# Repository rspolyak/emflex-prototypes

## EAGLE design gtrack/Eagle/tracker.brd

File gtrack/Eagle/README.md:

This folder contains schematic, PCB and gerber files for GSM security board.
Created using Eagle CAD version 7.7

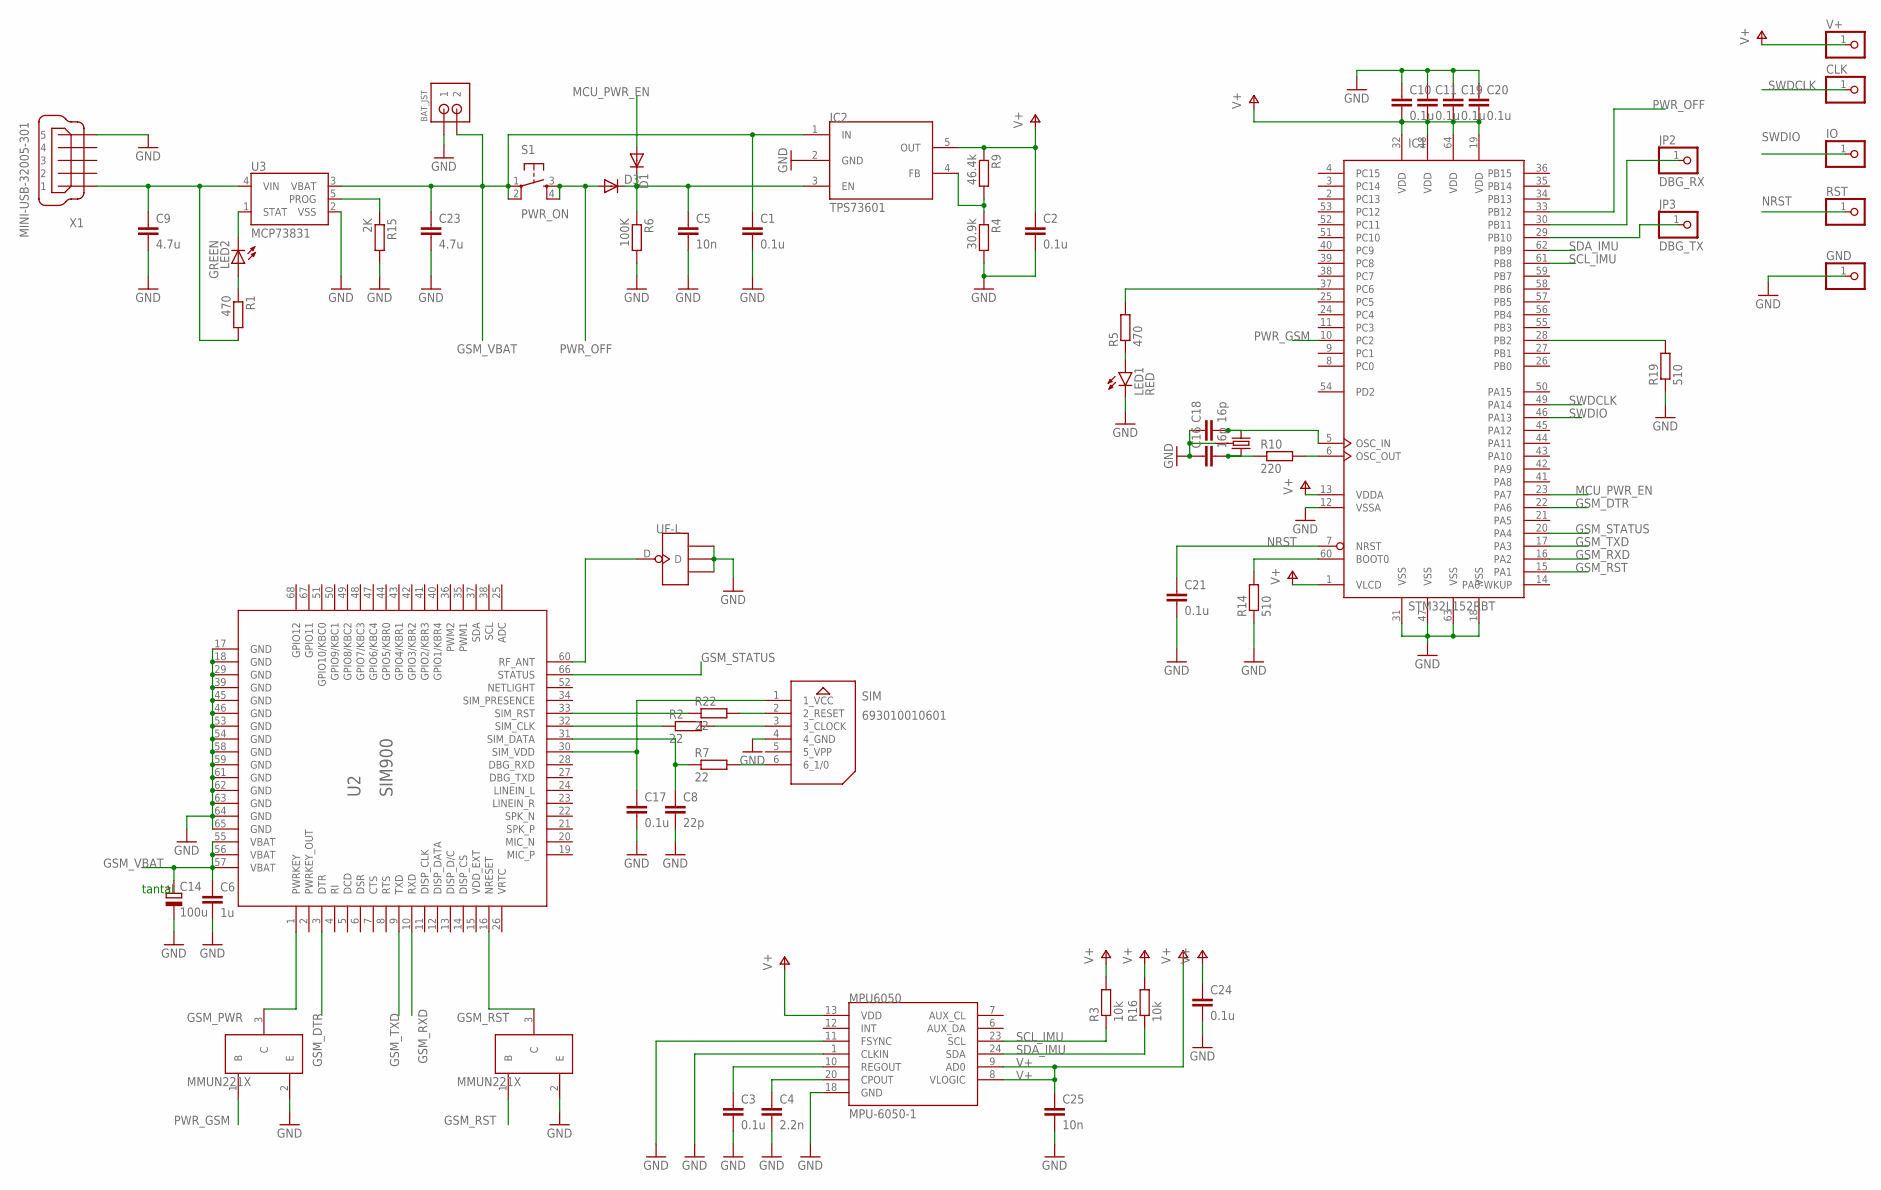
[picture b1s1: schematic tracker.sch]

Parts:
BAT_JST: JST-PH_2-PIN_HEADER; JST_B2B-PH_HEADER
C1, C2, C3, C10, C11, C17, C19, C20, C21, C24: 0.1u; C0805
C4: 2.2n; C0805
C5, C25: 10n; C0805
C6: 1u; C0805
C8: 22p; C0805
C9, C23: 4.7u; C0805
C14: 100u; C/6032-28R
C16, C18: 16p; C0603
CLK: PINHD-1X1; 1X01
CRTL: CRYSTAL-GROUNDED; CRYSTAL-SMD-5X3
D1, D3: MBR0520LT; SOD123
GND: PINHD-1X1; 1X01
GSM_PWR: MMUN221X
GSM_RST: MMUN221X
IC1: STM32L152RBT; LQFP64
IC2: TPS73601; SOT23
IO: PINHD-1X1; 1X01
JP2: DBG_RX; 1X01
JP3: DBG_TX; 1X01
LED1: RED; LED-0603
LED2: GREEN; LED-0603
MPU6050: MPU-6050-1; QFN-24-4MM2
R1, R5: 470; R0805
R2, R7, R22: 22; R0805
R3, R16: 10k; R0805
R4: 30.9k; R0805
R6: 100K; R0805
R9: 46.4k; R0805
R10: 220; R0805
R14, R19: 510; R0805
R15: 2K; R0805
RST: PINHD-1X1; 1X01
S1: PWR_ON; TACTILE-PTH
SIM: 693010010601
U2: SIM900
U3: MCP73831; SOT23-5
UF-L: ANTENNA-U-FL; 4P-U-FL
V+: PINHD-1X1; 1X01
X1: MINI-USB-32005-301; 32005-301

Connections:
BOOT1: IC1.28 (PB2), R19.2
DBG_RX: IC1.30 (PB11), JP2.1
DBG_TX: IC1.29 (PB10), JP3.1
GND: BAT_JST.P1 (1), C1.2, C2.2, C3.2, C4.2, C5.2, C6.2, C8.2, C9.2, C10.1, C11.1, C14.-, C16.1, C17.2, C18.1, C19.1, C20.1, C21.2, C23.2, C24.2, C25.2, CRTL.2 (3), CRTL.4 (3), GND.1, GSM_PWR.2 (E), GSM_RST.2 (E), IC1.12 (VSSA), IC1.18 (VSS), IC1.31 (VSS), IC1.47 (VSS), IC1.63 (VSS), IC2.2 (GND), LED1.C, MPU6050.1 (CLKIN), MPU6050.11 (FSYNC), MPU6050.18 (GND), R4.2, R6.2, R14.1, R15.2, R19.1, SIM.4 (4_GND), U2.17 (GND), U2.18 (GND), U2.29 (GND), U2.39 (GND), U2.45 (GND), U2.46 (GND), U2.53 (GND), U2.54 (GND), U2.58 (GND), U2.59 (GND), U2.61 (GND), U2.62 (GND), U2.63 (GND), U2.64 (GND), U2.65 (GND), U3.2 (VSS), UF-L.GND1, UF-L.GND2, UF-L.GND3, X1.5
GSM_DTR: IC1.22 (PA6), U2.3 (DTR)
GSM_RST: GSM_RST.1 (B), IC1.15 (PA1)
GSM_RXD: IC1.16 (PA2), U2.10 (RXD)
GSM_STATUS: IC1.20 (PA4), U2.66 (STATUS)
GSM_TXD: IC1.17 (PA3), U2.9 (TXD)
GSM_VBAT: BAT_JST.P2 (2), C1.1, C6.1, C14.+, C23.1, IC2.1 (IN), S1.1, S1.2, U2.55 (VBAT), U2.56 (VBAT), U2.57 (VBAT), U3.3 (VBAT)
MCU_PWR_EN: D1.A, IC1.23 (PA7)
unnamed: U2.60 (RF_ANT), UF-L.D
unnamed: R7.2, SIM.6 (6_1/0)
unnamed: GSM_RST.3 (C), U2.16 (NRESET)
unnamed: R2.2, SIM.3 (3_CLOCK)
unnamed: R22.2, SIM.2 (2_RESET)
unnamed: IC1.37 (PC6), R5.2
unnamed: C18.2, CRTL.3 (1), IC1.5 (OSC_IN)
unnamed: C16.2, CRTL.1 (2), R10.1
unnamed: LED2.A, R1.1
unnamed: IC2.4 (FB), R4.1, R9.2
unnamed: IC1.6 (OSC_OUT), R10.2
unnamed: IC1.60 (BOOT0), R14.2
unnamed: GSM_PWR.3 (C), U2.1 (PWRKEY)
unnamed: LED1.A, R5.1
unnamed: C4.1, MPU6050.20 (CPOUT)
unnamed: C3.1, MPU6050.10 (REGOUT)
NRST: C21.1, IC1.7 (NRST), RST.1
PROG: R15.1, U3.5 (PROG)
PWR_GSM: GSM_PWR.1 (B), IC1.10 (PC2)
PWR_OFF: D3.A, IC1.33 (PB12), S1.3, S1.4
SCL_IMU: IC1.61 (PB8), MPU6050.23 (SCL), R3.1
SDA_IMU: IC1.62 (PB9), MPU6050.24 (SDA), R16.1
SIM_CLK: R2.1, U2.32 (SIM_CLK)
SIM_DATA: C8.1, R7.1, U2.31 (SIM_DATA)
SIM_RST: R22.1, U2.33 (SIM_RST)
SIM_VDD: C17.1, SIM.1 (1_VCC), U2.30 (SIM_VDD)
STAT: LED2.C, U3.1 (STAT)
SWDCLK: CLK.1, IC1.49 (PA14)
SWDIO: IC1.46 (PA13), IO.1
V+: C2.1, C10.2, C11.2, C19.2, C20.2, C24.1, C25.1, IC1.1 (VLCD), IC1.13 (VDDA), IC1.19 (VDD), IC1.32 (VDD), IC1.48 (VDD), IC1.64 (VDD), IC2.5 (OUT), MPU6050.8 (VLOGIC), MPU6050.9 (AD0), MPU6050.13 (VDD), R3.2, R9.1, R16.2, V+.1
VCC_GSM: C5.1, D1.C, D3.C, IC2.3 (EN), R6.1
VIN1: C9.1, R1.2, U3.4 (VIN), X1.1

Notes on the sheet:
tantal

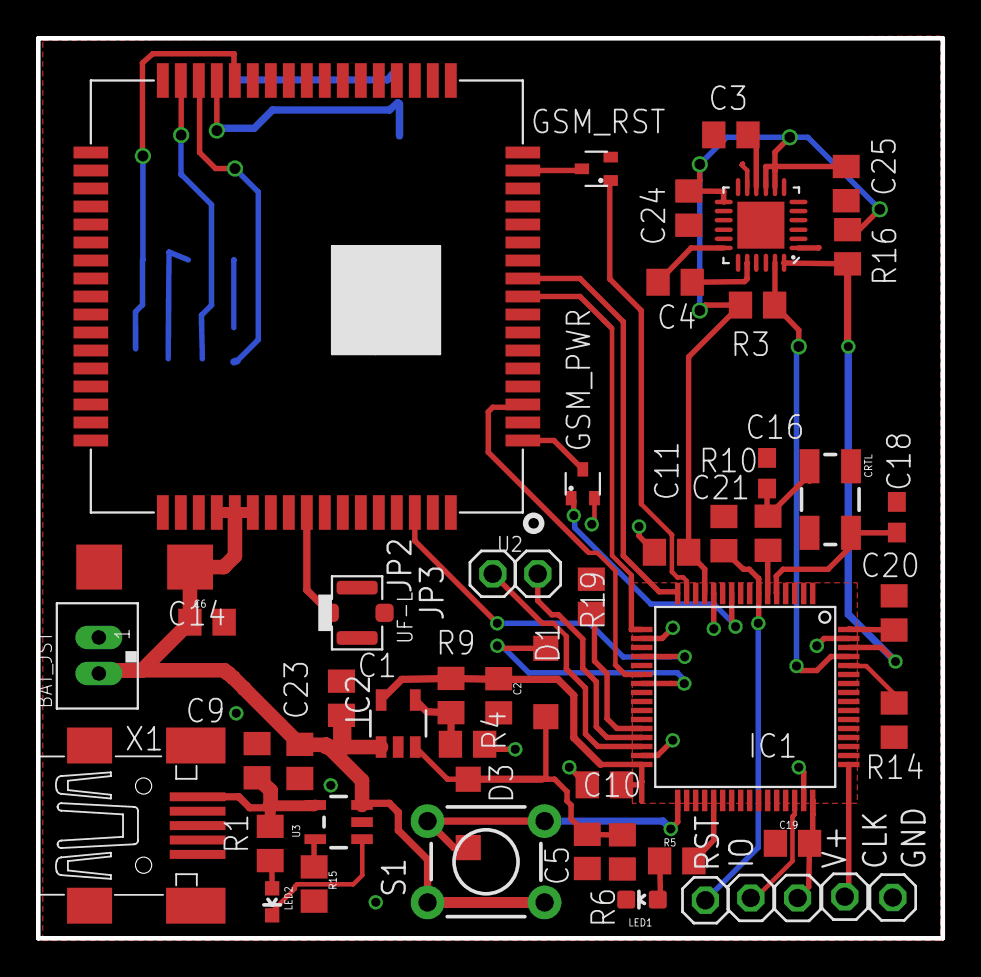
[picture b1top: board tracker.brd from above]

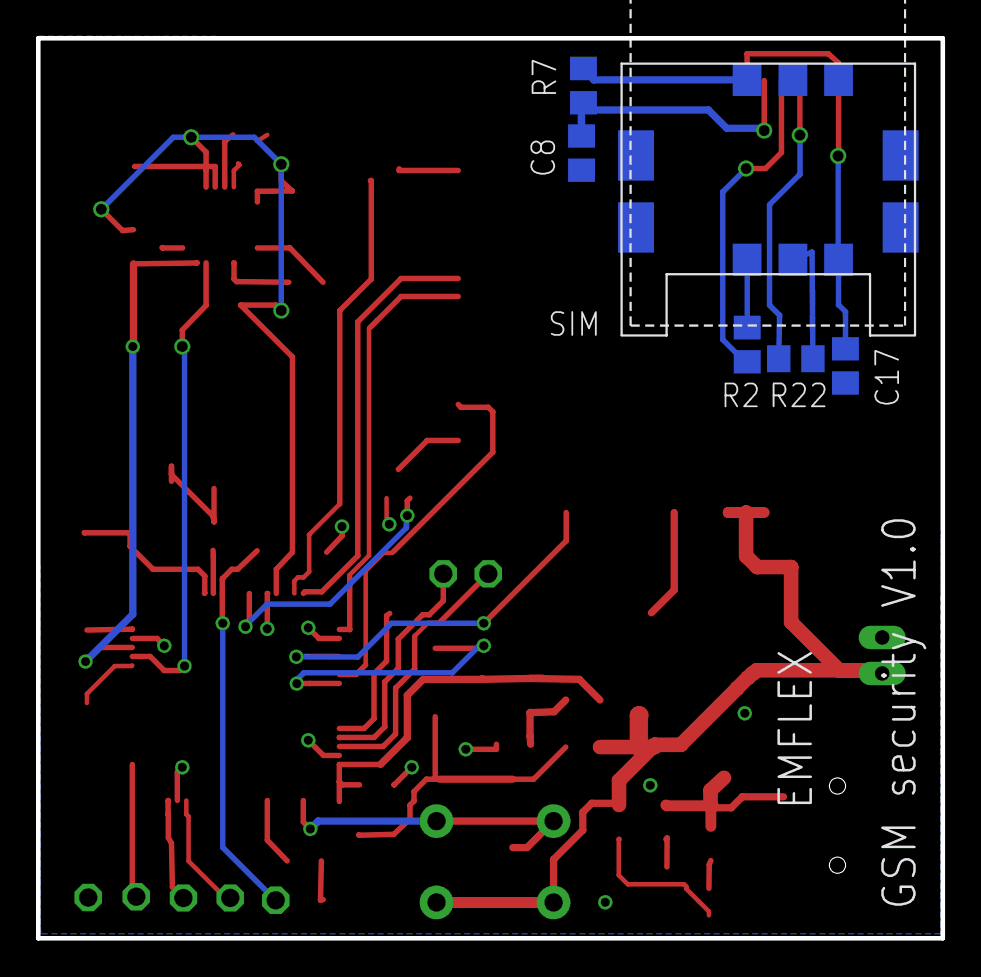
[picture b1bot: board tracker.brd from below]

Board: 2 copper layers, 50.2 x 50.0 mm, 58 parts (6 on the bottom side), 43 nets.

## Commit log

2016-12-30 Schematic, PCB, gerber for GSM security board
2017-01-10 Increase pad distance
2017-02-05 Fixed issue with missing MPU6050 power trace
2017-02-11 Specified board name and version
2017-02-15 Add battery connector to PCB
2017-03-11 Couple of PCB photos

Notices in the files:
parts and their libraries:
Speicherkarten-SockelWR-CRD: Copyright: Würth Elektronik
SparkFun-Electromechanical: Licensing: Creative Commons ShareAlike 4.0 International - https://creativecommons.org/licenses/by-sa/4.0
